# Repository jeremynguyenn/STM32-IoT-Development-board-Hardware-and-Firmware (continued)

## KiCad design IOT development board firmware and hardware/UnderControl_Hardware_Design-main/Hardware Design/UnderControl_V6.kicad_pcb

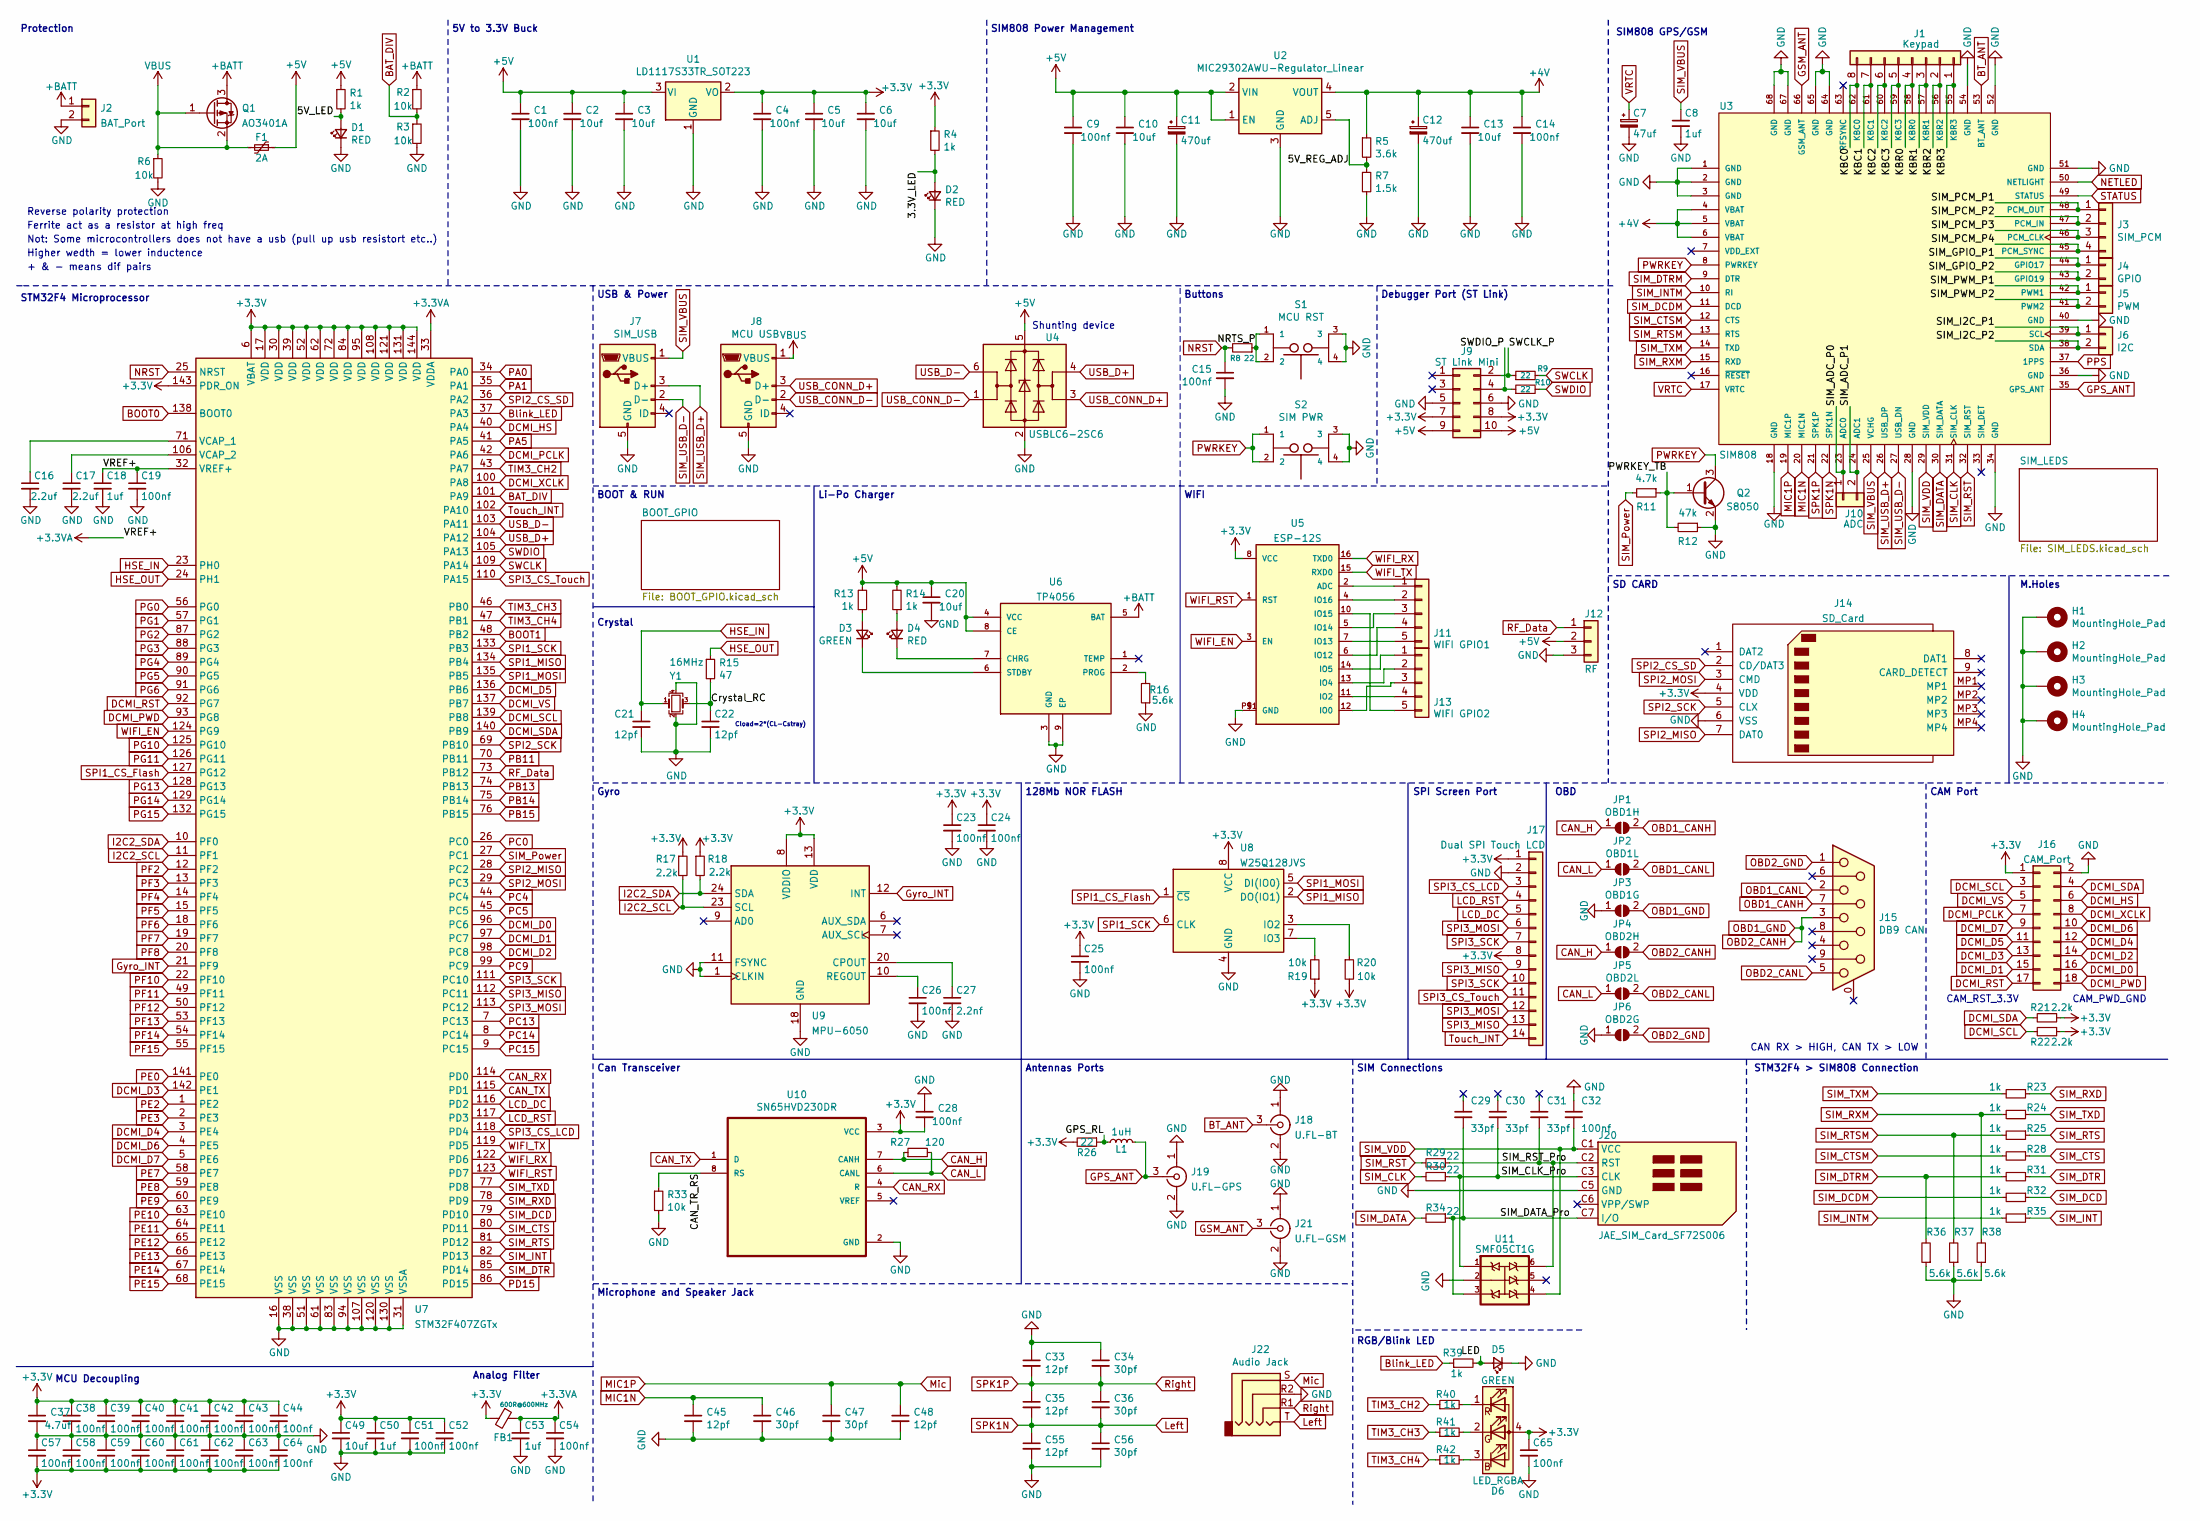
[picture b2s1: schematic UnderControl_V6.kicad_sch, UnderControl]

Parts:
C1, C4, C9, C14, C15, C19, C23, C24, C25, C26, C28, C32, C38, C39, C40, C41, C42, C43, C44, C51, C52, C54, C57, C58, C59, C60, C61, C62, C63, C64, C65: 100nf; C_0402_1005Metric; LCSC C1525
C2, C3, C5, C6, C10, C13, C20, C49: 10uf; C_0603_1608Metric; LCSC C19702
C7: 47uf; C_1206_3216Metric; LCSC C96123
C8, C18, C50, C53: 1uf; C_0402_1005Metric; LCSC C52923
C11, C12: 470uf; CP_Elec_6.3x7.7; LCSC C134738
C16, C17: 2.2uf; C_0402_1005Metric; LCSC C12530
C21, C22, C33, C35, C45, C48, C55: 12pf; C_0402_1005Metric; LCSC C1547
C27: 2.2nf; C_0402_1005Metric; LCSC C1531
C29, C30, C31: 33pf; C_0402_1005Metric; LCSC C1531
C34, C36, C46, C47, C56: 30pf; C_0402_1005Metric; LCSC C1570
C37: 4.7uf; C_0402_1005Metric; LCSC C23733
D1, D2, D4: RED; LED_0805_2012Metric; LCSC C84256
D3, D5: GREEN; LED_0603_1608Metric; LCSC C72043
D6: LED_RGBA; 19237R6GHBHCA012T; LCSC C60105
F1: 2A; Fuse_1206_3216Metric; LCSC C187595
FB1: 600R@600MHz; L_0805_2012Metric; LCSC C1017
H1, H2, H3, H4: MountingHole_Pad; MountingHole_2.5mm_Pad_Via
J1: Keypad; PinSocket_1x08_P2.54mm_Vertical
J2: BAT_Port; JST_B2B-XH-A(LF)(SN)
J3: SIM_PCM; PinHeader_1x04_P2.54mm_Vertical
J4: GPIO; PinHeader_1x02_P2.54mm_Vertical
J5: PWM; PinHeader_1x02_P2.54mm_Vertical
J6: I2C; PinHeader_1x02_P2.54mm_Vertical
J7: SIM_USB; AMPHENOL_10118194-0001LF; LCSC C132563
J8: MCU USB; AMPHENOL_10118194-0001LF; LCSC C132563
J9: ST Link Mini; PinSocket_2x05_P2.54mm_Horizontal
J10: ADC; PinHeader_1x02_P2.54mm_Vertical
J11: WIFI GPIO1; PinSocket_1x05_P2.54mm_Vertical
J12: RF; PinHeader_1x03_P2.54mm_Vertical
J13: WIFI GPIO2; PinSocket_1x05_P2.54mm_Vertical
J14: SD_Card; TF15X15; LCSC C111196
J15: DB9 CAN; DSUB-9_Female_Horizontal_P2.77x2.84mm_EdgePinOffset4.94mm_H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
J16: CAM_Port; PinSocket_2x09_P2.54mm_Vertical
J17: Dual SPI Touch LCD; PinSocket_1x14_P2.54mm_Vertical
J18: U.FL-BT; HRS_U.FL-R-SMT(01); LCSC C88374
J19: U.FL-GPS; HRS_U.FL-R-SMT(01); LCSC C88374
J20: JAE_SIM_Card_SF72S006; GCT_SIM8060-6-1-14-00-A; LCSC C410356
J21: U.FL-GSM; HRS_U.FL-R-SMT(01); LCSC C88374
J22: Audio Jack; Jack_3.5mm_PJ320D_Horizontal
JP1: OBD1H; SolderJumper-2_P1.3mm_Open_TrianglePad1.0x1.5mm
JP2: OBD1L; SolderJumper-2_P1.3mm_Open_TrianglePad1.0x1.5mm
JP3: OBD1G; SolderJumper-2_P1.3mm_Open_TrianglePad1.0x1.5mm
JP4: OBD2H; SolderJumper-2_P1.3mm_Open_TrianglePad1.0x1.5mm
JP5: OBD2L; SolderJumper-2_P1.3mm_Open_TrianglePad1.0x1.5mm
JP6: OBD2G; SolderJumper-2_P1.3mm_Open_TrianglePad1.0x1.5mm
L1: 1uH; L_0805_2012Metric; LCSC C1042
Q1: AO3401A; SOT-23; LCSC C15127
Q2: S8050; SOT-23; LCSC C2146
R1, R4, R13, R14, R23, R24, R25, R28, R31, R32, R35, R39, R40, R41, R42: 1k; R_0402_1005Metric; LCSC C11702
R2, R3, R6, R19, R20, R33: 10k; R_0402_1005Metric; LCSC C25744
R5: 3.6k; R_0603_1608Metric; LCSC C22980
R7: 1.5k; R_0603_1608Metric; LCSC C22843
R8, R9, R10, R26, R29, R30, R34: 22; R_0402_1005Metric; LCSC C25092
R11: 4.7k; R_0402_1005Metric; LCSC C25900
R12: 47k; R_0402_1005Metric; LCSC C25792
R15: 47; R_0402_1005Metric; LCSC C25118
R16, R36, R37, R38: 5.6k; R_0402_1005Metric; LCSC C25908
R17, R18, R21, R22: 2.2k; R_0402_1005Metric; LCSC C25879
R27: 120; R_0402_1005Metric; LCSC C25079
S1: MCU RST; SW_TL3342F160QG; LCSC C318884
S2: SIM PWR; SW_TL3342F160QG; LCSC C318884
U1: LD1117S33TR_SOT223; SOT-223-3_TabPin2; LCSC C86781
U2: MIC29302AWU-Regulator_Linear; TO-263-5_TabPin3; LCSC C411869
U3: SIM808; XCVR_SIM808; LCSC C126275
U4: USBLC6-2SC6; SOT-23-6; LCSC C2827654
U5: ESP-12S; LCSC C82898
U6: TP4056; SOIC127P600X175-9N; LCSC C16581
U7: STM32F407ZGTx; LQFP-144_20x20mm_P0.5mm; LCSC C19156
U8: W25Q128JVS; SOIC-8_5.23x5.23mm_P1.27mm; LCSC C97521
U9: MPU-6050; InvenSense_QFN-24_4x4mm_P0.5mm_NoMask; LCSC C24112
U10: SN65HVD230DR; SOIC127P599X175-8N; LCSC C12084
U11: SMF05CT1G; SOT65P210X110-6N; LCSC C15879
Y1: 16MHz; Crystal_SMD_3225-4Pin_3.2x2.5mm; LCSC C13738

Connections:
+3.3VA: C18.1, C19.1, C53.1, C54.1, FB1.1, U7.32 (VREF+), U7.33 (VDDA)
+3V3: C4.1, C5.1, C6.1, C23.1, C24.1, C25.1, C28.2, C37.1, C38.1, C39.1, C40.1, C41.1, C42.1, C43.1, C44.1, C49.1, C50.1, C51.1, C52.1, C57.2, C58.2, C59.2, C60.2, C61.2, C62.2, C63.2, C64.2, C65.1, D6.4 (A), FB1.2, J9.7, J9.8, J14.4 (VDD), J16.1, J17.1, J17.8, R4.1, R17.1, R18.1, R19.1, R20.2, R21.1, R22.1, R26.2, U1.2 (VO), U5.8 (VCC), U7.6 (VBAT), U7.17 (VDD), U7.30 (VDD), U7.39 (VDD), U7.52 (VDD), U7.62 (VDD), U7.72 (VDD), U7.84 (VDD), U7.95 (VDD), U7.108 (VDD), U7.121 (VDD), U7.131 (VDD), U7.143 (PDR_ON), U7.144 (VDD), U8.8 (VCC), U9.8 (VDDIO), U9.13 (VDD), U10.3 (VCC); also elsewhere on the board
+4V: C12.1, C13.1, C14.1, R5.1, U2.4 (VOUT), U3.4 (VBAT), U3.5 (VBAT), U3.6 (VBAT)
+5V: C1.1, C2.1, C3.1, C9.1, C10.1, C11.1, C20.1, F1.1, J9.9, J9.10, J12.2, R1.1, R13.2, R14.2, U1.3 (VI), U2.1 (EN), U2.2 (VIN), U4.5 (VBUS), U6.4 (VCC), U6.8 (CE); also elsewhere on the board
+BATT: J2.1, Q1.3 (D), R2.1, U6.5 (BAT)
/3.3V_LED: D2.2 (A), R4.2
/5V_LED: D1.2 (A), R1.2
/5V_REG_ADJ: R5.2, R7.1, U2.5 (ADJ)
/CAN_TR_RS: R33.1, U10.8 (RS)
/Crystal_RC: C22.1, R15.2, Y1.3
/GPS_RL: L1.1, R26.1
/KBC0: J1.8, U3.62 (KBC0)
/KBC1: J1.7, U3.61 (KBC1)
/KBC2: J1.6, U3.60 (KBC2)
/KBC3: J1.5, U3.59 (KBC3)
/KBR0: J1.4, U3.58 (KBR0)
/KBR1: J1.3, U3.57 (KBR1)
/KBR2: J1.2, U3.56 (KBR2)
/KBR3: J1.1, U3.55 (KBR3)
/LED: D5.2 (A), R39.2
/NRTS_P: R8.1, S1.1, S1.2
/PWRKEY_TB: Q2.1 (B), R11.1, R12.2
/SIM_ADC_P0: J10.1, U3.23 (ADC0)
/SIM_ADC_P1: J10.2, U3.24 (ADC1)
/SIM_CLK_Pro: C30.2, J20.C3 (CLK), R30.1, U11.1
/SIM_DATA_Pro: C29.2, J20.C7 (I/O), R34.1, U11.3
/SIM_GPIO_P1: J4.1, U3.44 (GPIO17)
/SIM_GPIO_P2: J4.2, U3.43 (GPIO19)
/SIM_I2C_P1: J6.1, U3.39 (SCL)
/SIM_I2C_P2: J6.2, U3.38 (SDA)
/SIM_PCM_P1: J3.1, U3.48 (PCM_OUT)
/SIM_PCM_P2: J3.2, U3.47 (PCM_IN)
/SIM_PCM_P3: J3.3, U3.46 (PCM_CLK)
/SIM_PCM_P4: J3.4, U3.45 (PCM_SYNC)
/SIM_PWM_P1: J5.1, U3.42 (PWM1)
/SIM_PWM_P2: J5.2, U3.41 (PWM2)
/SIM_RST_Pro: C31.2, J20.C2 (RST), R29.1, U11.6
/SWCLK_P: J9.2, R9.1
/SWDIO_P: J9.4, R10.1
BAT_DIV: R2.2, R3.1, U7.101 (PA9)
BOOT0: U7.138 (BOOT0); also elsewhere on the board
BOOT1: U7.48 (PB2); also elsewhere on the board
BT_ANT: J18.3 (GND), U3.53 (BT_ANT)
Blink_LED: R39.1, U7.37 (PA3)
CAN_H: JP1.1 (A), JP4.1 (A), R27.1, U10.7 (CANH)
CAN_L: JP2.1 (A), JP5.1 (A), R27.2, U10.6 (CANL)
CAN_RX: U7.114 (PD0), U10.4 (R)
CAN_TX: U7.115 (PD1), U10.1 (D)
DCMI_D0: J16.16, U7.96 (PC6)
DCMI_D1: J16.15, U7.97 (PC7)
DCMI_D2: J16.14, U7.98 (PC8)
DCMI_D3: J16.13, U7.142 (PE1)
DCMI_D4: J16.12, U7.3 (PE4)
DCMI_D5: J16.11, U7.136 (PB6)
DCMI_D6: J16.10, U7.4 (PE5)
DCMI_D7: J16.9, U7.5 (PE6)
DCMI_HS: J16.6, U7.40 (PA4)
DCMI_PCLK: J16.7, U7.42 (PA6)
DCMI_PWD: J16.18, U7.93 (PG8)
DCMI_RST: J16.17, U7.92 (PG7)
DCMI_SCL: J16.3, R22.2, U7.139 (PB8)
DCMI_SDA: J16.4, R21.2, U7.140 (PB9)
DCMI_VS: J16.5, U7.137 (PB7)
DCMI_XCLK: J16.8, U7.100 (PA8)
GND: C1.2, C2.2, C3.2, C4.2, C5.2, C6.2, C7.2, C8.2, C9.2, C10.2, C11.2, C12.2, C13.2, C14.2, C15.2, C16.2, C17.2, C18.2, C19.2, C20.2, C21.2, C22.2, C23.2, C24.2, C25.2, C26.2, C27.2, C28.1, C32.1, C33.1, C34.1, C37.2, C38.2, C39.2, C40.2, C41.2, C42.2, C43.2, C44.2, C45.2, C46.2, C47.2, C48.2, C49.2, C50.2, C51.2, C52.2, C53.2, C54.2, C55.2, C56.2, C57.1, C58.1, C59.1, C60.1, C61.1, C62.1, C63.1, C64.1, C65.2, D1.1 (K), D2.1 (K), D5.1 (K), H1.1, H2.1, H3.1, H4.1, J2.2, J7.5 (GND), J8.5 (GND), J9.5, J9.6, J12.3, J14.6 (VSS), J16.2, J17.2, J18.1 (In), J18.2 (GND), J19.1 (In), J19.2 (GND), J20.C5 (GND), J21.1 (In), J21.2 (GND), J22.R2, JP3.1 (A), JP6.1 (A), Q2.2 (E), R3.2, R6.2, R7.2, R12.1, R16.1, R33.2, R36.1, R37.1, R38.1, S1.3, S1.4, S2.3, S2.4, U1.1 (GND), U2.3 (GND), U3.1 (GND), U3.2 (GND), U3.3 (GND), U3.18 (GND), U3.28 (GND), U3.34 (GND), U3.36 (GND), U3.40 (GND), U3.51 (GND), U3.52 (GND), U3.54 (GND), U3.64 (GND), U3.65 (GND), U3.67 (GND), U3.68 (GND), U4.2 (GND), U5.9 (GND), U5.P$1 (GND), U6.3 (GND), U6.9 (EP), U7.16 (VSS), U7.31 (VSSA), U7.38 (VSS), U7.51 (VSS), U7.61 (VSS), U7.83 (VSS), U7.94 (VSS), U7.107 (VSS), U7.120 (VSS), U7.130 (VSS), U8.4 (GND), U9.1 (CLKIN), U9.11 (FSYNC), U9.18 (GND), U10.2 (GND), U11.2, Y1.2, Y1.4; also elsewhere on the board
GPS_ANT: J19.3 (GND), L1.2, U3.35 (GPS_ANT)
GSM_ANT: J21.3 (GND), U3.66 (GSM_ANT)
Gyro_INT: U7.21 (PF9), U9.12 (INT)
HSE_IN: C21.1, U7.23 (PH0), Y1.1
HSE_OUT: R15.1, U7.24 (PH1)
I2C2_SCL: R17.2, U7.11 (PF1), U9.23 (SCL)
I2C2_SDA: R18.2, U7.10 (PF0), U9.24 (SDA)
LCD_DC: J17.5, U7.116 (PD2)
LCD_RST: J17.4, U7.117 (PD3)
Left: C35.2, C36.2, C55.1, C56.1, J22.T, U3.22 (SPK1N)
MIC1N: C45.1, C46.1, U3.20 (MIC1N)
MIC1P: C47.1, C48.1, J22.S, U3.19 (MIC1P)
NETLED: U3.50 (NETLIGHT); also elsewhere on the board
NRST: C15.1, R8.2, U7.25 (NRST)
unnamed: C16.1, U7.71 (VCAP_1)
unnamed: C17.1, U7.106 (VCAP_2)
unnamed: C26.1, U9.10 (REGOUT)
unnamed: C27.1, U9.20 (CPOUT)
unnamed: D3.1 (K), U6.6 (STDBY)
unnamed: D3.2 (A), R13.1
unnamed: D4.1 (K), U6.7 (CHRG)
unnamed: D4.2 (A), R14.1
unnamed: D6.1 (RK), R40.2
unnamed: D6.2 (GK), R41.2
unnamed: D6.3 (BK), R42.2
unnamed: J11.1, U5.2 (ADC)
unnamed: J11.2, U5.4 (IO16)
unnamed: J11.3, U5.5 (IO14)
unnamed: J11.4, U5.6 (IO12)
unnamed: J11.5, U5.7 (IO13)
unnamed: J13.1, U5.14 (IO5)
unnamed: J13.2, U5.13 (IO4)
unnamed: J13.3, U5.12 (IO0)
unnamed: J13.4, U5.11 (IO2)
unnamed: J13.5, U5.10 (IO15)
unnamed: R16.2, U6.2 (PROG)
unnamed: R19.2, U8.7 (IO3)
unnamed: R20.1, U8.3 (IO2)
OBD1_CANH: J15.7, JP1.2 (B)
OBD1_CANL: J15.2, JP2.2 (B)
OBD1_GND: J15.3, JP3.2 (B), JP4.2 (B)
OBD2_CANL: J15.5, JP5.2 (B)
OBD2_GND: J15.1, JP6.2 (B)
PA0: U7.34 (PA0)
PA1: U7.35 (PA1)
PA5: U7.41 (PA5)
PB11: U7.70 (PB11)
PB13: U7.74 (PB13)
PB14: U7.75 (PB14)
PB15: U7.76 (PB15)
PC0: U7.26 (PC0)
PC4: U7.44 (PC4)
PC5: U7.45 (PC5)
PC9: U7.99 (PC9); also elsewhere on the board
PC13: U7.7 (PC13)
PC14: U7.8 (PC14)
PC15: U7.9 (PC15)
PD15: U7.86 (PD15)
PE0: U7.141 (PE0)
PE2: U7.1 (PE2)
PE3: U7.2 (PE3)
PE7: U7.58 (PE7); also elsewhere on the board
PE8: U7.59 (PE8); also elsewhere on the board
PE9: U7.60 (PE9)
PE10: U7.63 (PE10)
PE11: U7.64 (PE11); also elsewhere on the board
PE12: U7.65 (PE12)
PE13: U7.66 (PE13)
PE14: U7.67 (PE14)
PE15: U7.68 (PE15)
PF2: U7.12 (PF2); also elsewhere on the board
PF3: U7.13 (PF3); also elsewhere on the board
PF4: U7.14 (PF4); also elsewhere on the board
PF5: U7.15 (PF5)
PF6: U7.18 (PF6)
PF7: U7.19 (PF7); also elsewhere on the board
PF8: U7.20 (PF8); also elsewhere on the board
PF10: U7.22 (PF10)
PF11: U7.49 (PF11)
PF12: U7.50 (PF12)
PF13: U7.53 (PF13)
PF14: U7.54 (PF14)
PF15: U7.55 (PF15)
PG0: U7.56 (PG0); also elsewhere on the board
PG1: U7.57 (PG1); also elsewhere on the board
PG2: U7.87 (PG2); also elsewhere on the board
PG3: U7.88 (PG3); also elsewhere on the board
PG4: U7.89 (PG4); also elsewhere on the board
PG5: U7.90 (PG5); also elsewhere on the board
PG6: U7.91 (PG6)
PG10: U7.125 (PG10)
PG11: U7.126 (PG11)
PG13: U7.128 (PG13)
PG14: U7.129 (PG14)
PG15: U7.132 (PG15)
PPS: U3.37 (1PPS); also elsewhere on the board
PWRKEY: Q2.3 (C), S2.1, S2.2, U3.8 (PWRKEY)
RF_Data: J12.1, U7.73 (PB12)
Right: C33.2, C34.2, C35.1, C36.1, J22.R1, U3.21 (SPK1P)
SIM_CLK: R30.2, U3.31 (SIM_CLK)
SIM_CTS: R28.1, U7.80 (PD11)
SIM_CTSM: R28.2, U3.12 (CTS)
SIM_DATA: R34.2, U3.30 (SIM_DATA)
SIM_DCD: R32.1, U7.79 (PD10)
SIM_DCDM: R32.2, U3.11 (DCD)
SIM_DTR: R31.1, U7.85 (PD14)
SIM_DTRM: R31.2, R36.2, U3.9 (DTR)
SIM_INT: R35.1, U7.82 (PD13)
SIM_INTM: R35.2, U3.10 (RI)
SIM_Power: R11.2, U7.27 (PC1)
SIM_RST: R29.2, U3.32 (SIM_RST)
SIM_RTS: R25.1, U7.81 (PD12)
SIM_RTSM: R25.2, R37.2, U3.13 (RTS)
SIM_RXD: R23.1, U7.78 (PD9)
SIM_RXM: R24.2, R38.2, U3.15 (RXD)
SIM_TXD: R24.1, U7.77 (PD8)
SIM_TXM: R23.2, U3.14 (TXD)
SIM_USB_D+: J7.3 (D+), U3.26 (USB_DP)
SIM_USB_D-: J7.2 (D-), U3.27 (USB_DN)
SIM_VBUS: C8.1, J7.1 (VBUS), U3.25 (VCHG)
SIM_VDD: C32.2, J20.C1 (VCC), U3.29 (SIM_VDD), U11.4
SPI1_CS_Flash: U7.127 (PG12), U8.1 (~CS)
SPI1_MISO: U7.134 (PB4), U8.2 (DO(IO1))
SPI1_MOSI: U7.135 (PB5), U8.5 (DI(IO0))
SPI1_SCK: U7.133 (PB3), U8.6 (CLK)
SPI2_CS_SD: J14.2 (CD/DAT3), U7.36 (PA2)
SPI2_MISO: J14.7 (DAT0), U7.28 (PC2)
SPI2_MOSI: J14.3 (CMD), U7.29 (PC3)
SPI2_SCK: J14.5 (CLX), U7.69 (PB10)
SPI3_CS_LCD: J17.3, U7.118 (PD4)
SPI3_CS_Touch: J17.11, U7.110 (PA15)
SPI3_MISO: J17.9, J17.13, U7.112 (PC11)
SPI3_MOSI: J17.6, J17.12, U7.113 (PC12)
SPI3_SCK: J17.7, J17.10, U7.111 (PC10)
STATUS: U3.49 (STATUS); also elsewhere on the board
SWCLK: R9.2, U7.109 (PA14)
SWDIO: R10.2, U7.105 (PA13)
TIM3_CH2: R40.1, U7.43 (PA7)
TIM3_CH3: R41.1, U7.46 (PB0)
TIM3_CH4: R42.1, U7.47 (PB1)
Touch_INT: J17.14, U7.102 (PA10)
USB_CONN_D+: J8.3 (D+), U4.3 (I/O2)
USB_CONN_D-: J8.2 (D-), U4.1 (I/O1)
USB_D+: U4.4 (I/O2), U7.104 (PA12)
USB_D-: U4.6 (I/O1), U7.103 (PA11)
VBUS: F1.2, J8.1 (VBUS), Q1.1 (G), Q1.2 (S), R6.1
VRTC: C7.1, U3.17 (VRTC)
WIFI_EN: U5.3 (EN), U7.124 (PG9)
WIFI_RST: U5.1 (RST), U7.123 (PD7)
WIFI_RX: U5.16 (TXD0), U7.122 (PD6)
WIFI_TX: U5.15 (RXD0), U7.119 (PD5)

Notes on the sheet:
Shunting device
128Mb NOR FLASH
OBD
Antennas Ports
CAM_PWD_GND
CAM Port
Ferrite act as a resistor at high freq
Gyro
Crystal
SPI Screen Port
Buttons
CAN RX > HIGH, CAN TX > LOW
Not: Some microcontrollers does not have a usb (pull up usb resistort etc..)
BOOT & RUN
RGB/Blink LED
SD CARD
Protection
Higher wedth = lower inductence
WIFI
Microphone and Speaker Jack
M.Holes
CAM_RST_3.3V
Li-Po Charger
Reverse polarity protection
Can Transceiver
SIM808 Power Management
STM32F4 > SIM808 Connection
USB & Power
5V to 3.3V Buck
MCU Decoupling
STM32F4 Microprocessor
SIM808 GPS/GSM
Cload=2*(CL-Cstray)
Debugger Port (ST Link)
SIM Connections
Analog Filter
+ & - means dif pairs

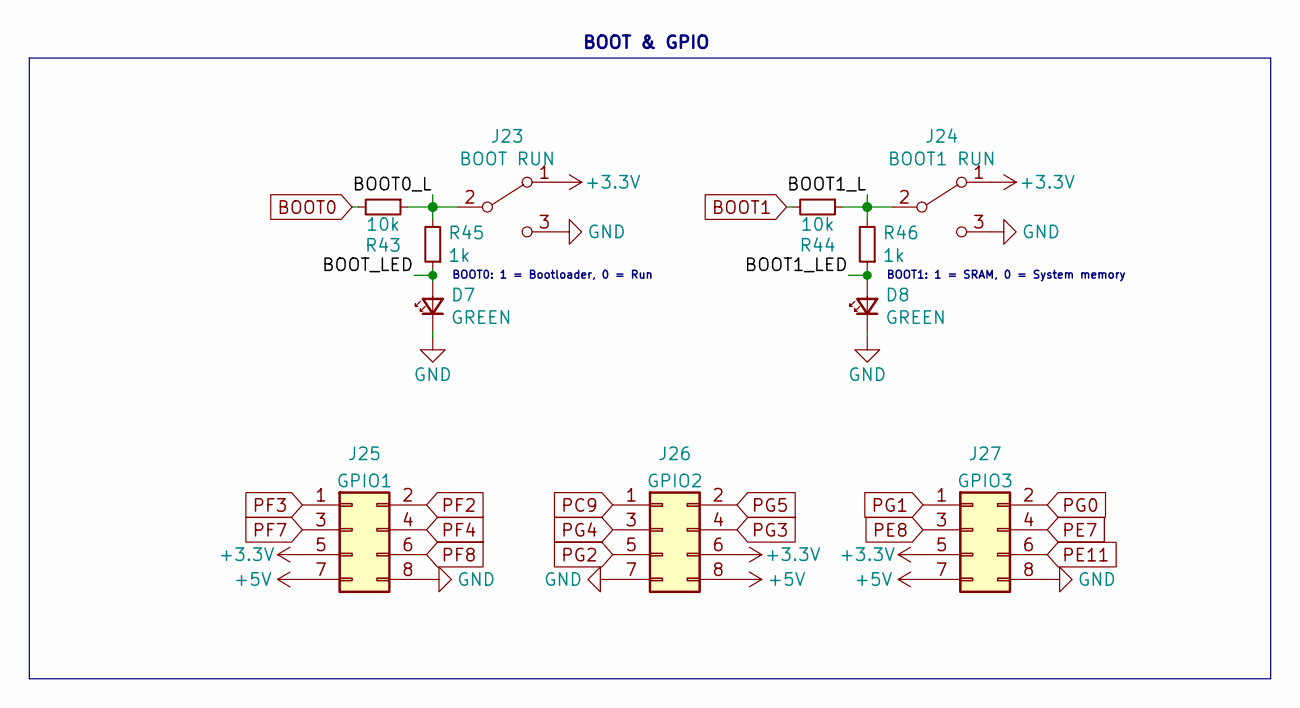
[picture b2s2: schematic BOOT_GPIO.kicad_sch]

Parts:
D7, D8: GREEN; LED_0603_1608Metric; LCSC C72043
J23: BOOT RUN; PinHeader_1x03_P2.54mm_Vertical
J24: BOOT1 RUN; PinHeader_1x03_P2.54mm_Vertical
J25: GPIO1; PinHeader_2x04_P2.54mm_Vertical
J26: GPIO2; PinHeader_2x04_P2.54mm_Vertical
J27: GPIO3; PinHeader_2x04_P2.54mm_Vertical
R43, R44: 10k; R_0402_1005Metric; LCSC C25744
R45, R46: 1k; R_0402_1005Metric; LCSC C11702

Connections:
+3V3: J23.1 (A), J24.1 (A), J25.5, J26.6, J27.5; also elsewhere on the board
+5V: J25.7, J26.8, J27.7; also elsewhere on the board
/BOOT_GPIO/BOOT0_L: J23.2 (B), R43.1, R45.2
/BOOT_GPIO/BOOT1_L: J24.2 (B), R44.1, R46.2
/BOOT_GPIO/BOOT1_LED: D8.2 (A), R46.1
/BOOT_GPIO/BOOT_LED: D7.2 (A), R45.1
BOOT0: R43.2; also elsewhere on the board
BOOT1: R44.2; also elsewhere on the board
GND: D7.1 (K), D8.1 (K), J23.3 (C), J24.3 (C), J25.8, J26.7, J27.8; also elsewhere on the board
PC9: J26.1; also elsewhere on the board
PE7: J27.4; also elsewhere on the board
PE8: J27.3; also elsewhere on the board
PE11: J27.6; also elsewhere on the board
PF2: J25.2; also elsewhere on the board
PF3: J25.1; also elsewhere on the board
PF4: J25.4; also elsewhere on the board
PF7: J25.3; also elsewhere on the board
PF8: J25.6; also elsewhere on the board
PG0: J27.2; also elsewhere on the board
PG1: J27.1; also elsewhere on the board
PG2: J26.5; also elsewhere on the board
PG3: J26.4; also elsewhere on the board
PG4: J26.3; also elsewhere on the board
PG5: J26.2; also elsewhere on the board

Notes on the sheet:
BOOT1: 1 = SRAM, 0 = System memory
BOOT & GPIO
BOOT0: 1 = Bootloader, 0 = Run

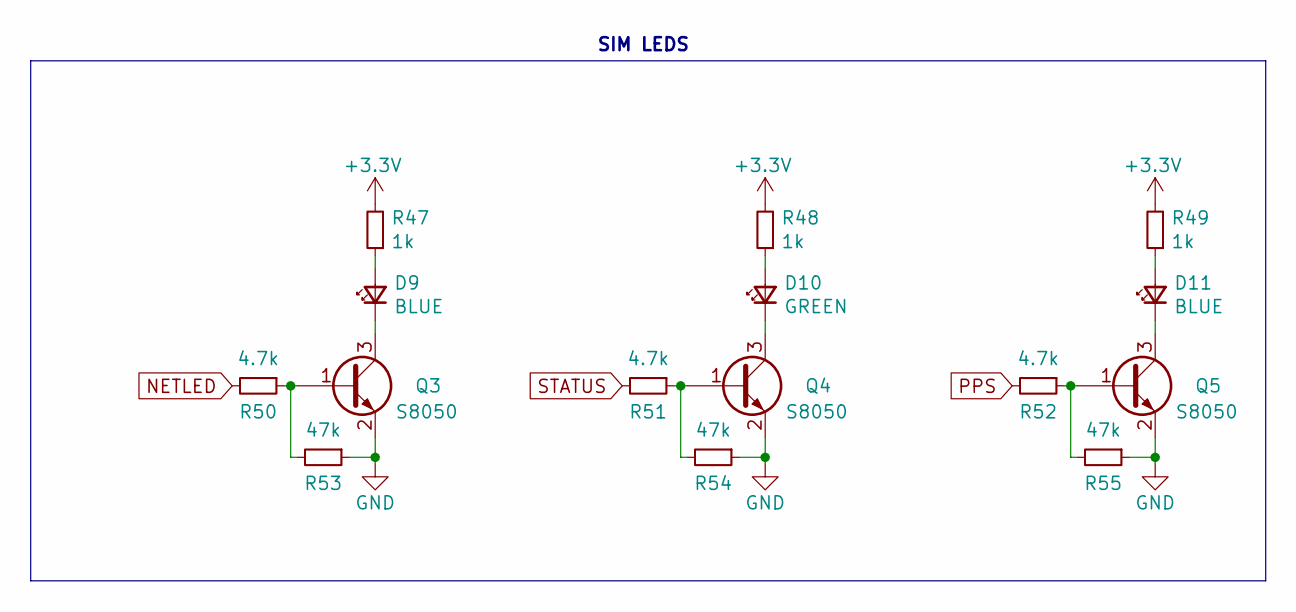
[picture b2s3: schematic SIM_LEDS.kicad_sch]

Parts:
D9, D11: BLUE; LED_0603_1608Metric; LCSC C72041
D10: GREEN; LED_0603_1608Metric; LCSC C72043
Q3, Q4, Q5: S8050; SOT-23; LCSC C2146
R47, R48, R49: 1k; R_0402_1005Metric; LCSC C11702
R50, R51, R52: 4.7k; R_0402_1005Metric; LCSC C25900
R53, R54, R55: 47k; R_0402_1005Metric; LCSC C25792

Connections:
+3V3: R47.2, R48.2, R49.2; also elsewhere on the board
GND: Q3.2 (E), Q4.2 (E), Q5.2 (E), R53.1, R54.1, R55.1; also elsewhere on the board
NETLED: R50.2; also elsewhere on the board
unnamed: D9.1 (K), Q3.3 (C)
unnamed: D9.2 (A), R47.1
unnamed: D10.1 (K), Q4.3 (C)
unnamed: D10.2 (A), R48.1
unnamed: D11.1 (K), Q5.3 (C)
unnamed: D11.2 (A), R49.1
unnamed: Q3.1 (B), R50.1, R53.2
unnamed: Q4.1 (B), R51.1, R54.2
unnamed: Q5.1 (B), R52.1, R55.2
PPS: R52.2; also elsewhere on the board
STATUS: R51.2; also elsewhere on the board

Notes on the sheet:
SIM LEDS

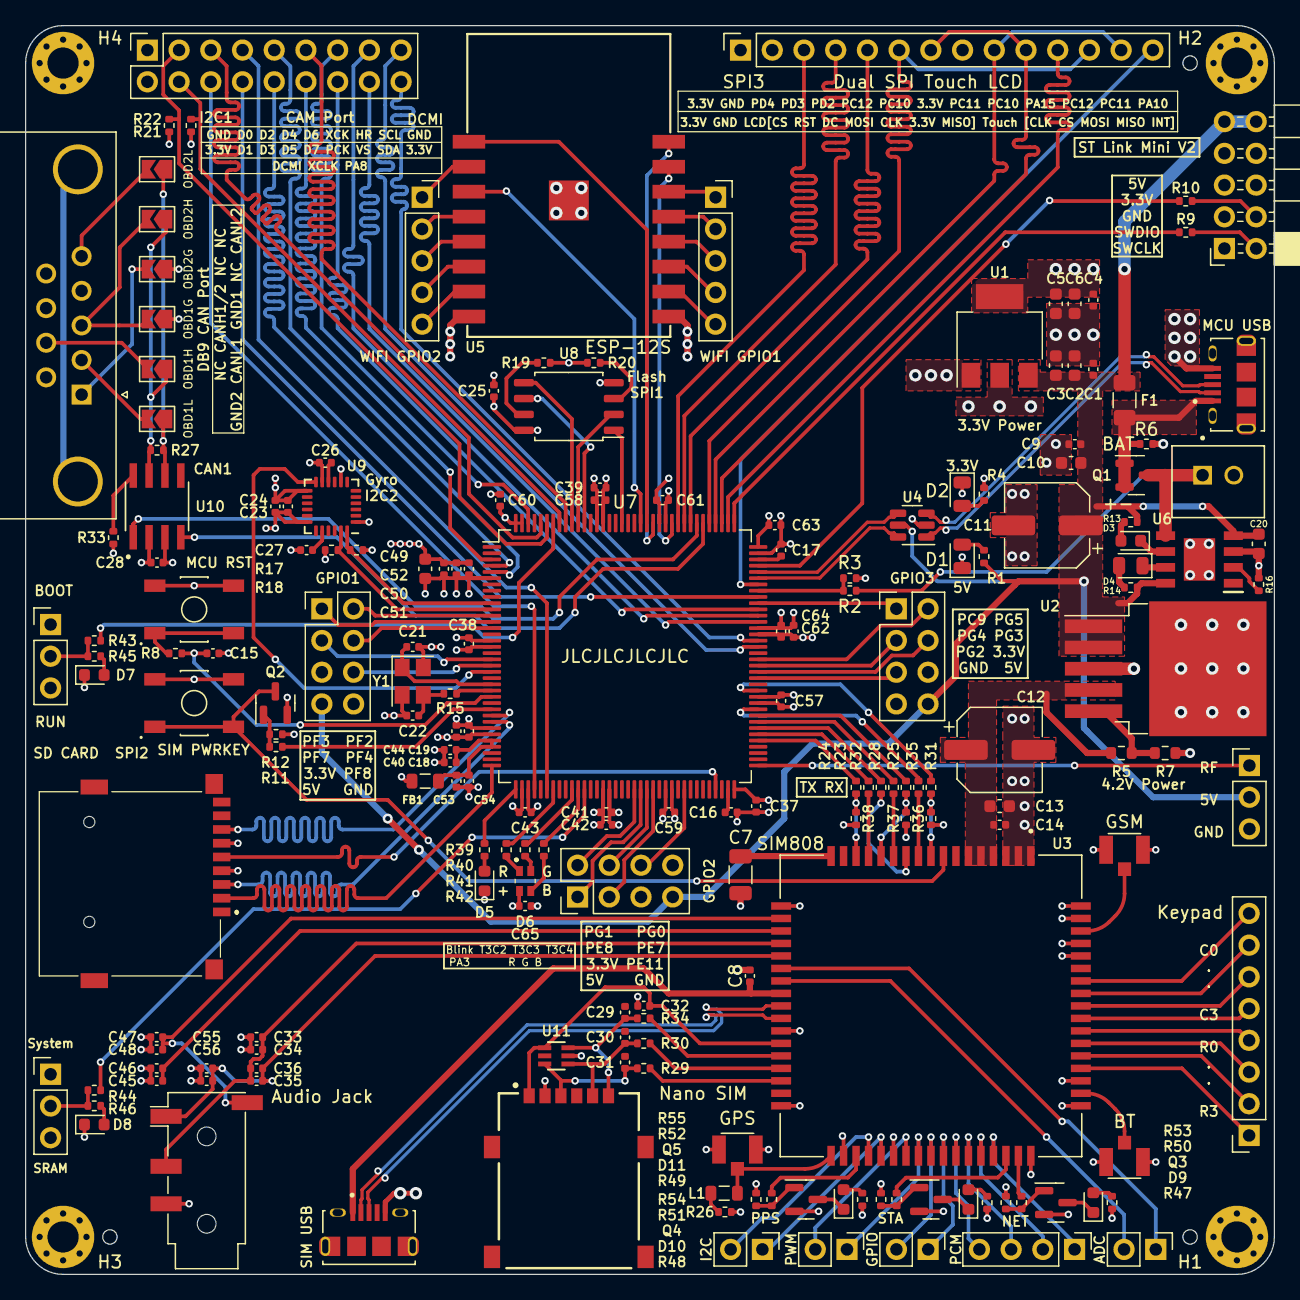
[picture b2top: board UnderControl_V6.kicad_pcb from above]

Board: 4 copper layers, 100.0 x 100.0 mm, 190 parts (0 on the bottom side), 192 nets.

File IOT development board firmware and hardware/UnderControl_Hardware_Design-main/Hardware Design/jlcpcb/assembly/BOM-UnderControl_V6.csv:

Comment,Designator,Footprint,LCSC
600R@600MHz,FB1,L_0805_2012Metric,C1017
1uH,L1,L_0805_2012Metric,C1042
SD_Card,J14,TF15X15,C111196
1k,"R1,R13,R14,R23,R24,R25,R28,R31,R32,R35,R39,R4,R40,R41,R42,R45,R46,R47,R48,R49",R_0402_1005Metric,C11702
SN65HVD230DR,U10,SOIC127P599X175-8N,C12084
2.2uf,"C16,C17",C_0402_1005Metric,C12530
SIM808,U3,XCVR_SIM808,C126275
SIM_USB,"J7,J8",AMPHENOL_10118194-0001LF,C132563
470uf,"C11,C12",CP_Elec_6.3x7.7,C134738
16MHz,Y1,Crystal_SMD_3225-4Pin_3.2x2.5mm,C13738
AO3401A,Q1,SOT-23,C15127
100nf,"C1,C14,C15,C19,C23,C24,C25,C26,C28,C32,C38,C39,C4,C40,C41,C42,C43,C44,C51,C52,C54,C57,C58,C59,C60,C61,C62,C63,C64,C65,C9",C_0402_1005Metric,C1525
2.2nf,"C27,C29,C30,C31",C_0402_1005Metric,C1531
12pf,"C21,C22,C33,C35,C45,C48,C55",C_0402_1005Metric,C1547
30pf,"C34,C36,C46,C47,C56",C_0402_1005Metric,C1570
SMF05CT1G,U11,SOT65P210X110-6N,C15879
TP4056,U6,SOIC127P600X175-9N,C16581
2A,F1,Fuse_1206_3216Metric,C187595
STM32F407ZGTx,U7,LQFP-144_20x20mm_P0.5mm,C19156
10uf,"C10,C13,C2,C20,C3,C49,C5,C6",C_0603_1608Metric,C19702
S8050,"Q2,Q3,Q4,Q5",SOT-23,C2146
1.5k,R7,R_0603_1608Metric,C22843
3.6k,R5,R_0603_1608Metric,C22980
4.7uf,C37,C_0402_1005Metric,C23733
MPU-6050,U9,InvenSense_QFN-24_4x4mm_P0.5mm_NoMask,C24112
120,R27,R_0402_1005Metric,C25079
22,"R10,R26,R29,R30,R34,R8,R9",R_0402_1005Metric,C25092
47,R15,R_0402_1005Metric,C25118
10k,"R19,R2,R20,R3,R33,R43,R44,R6",R_0402_1005Metric,C25744
47k,"R12,R53,R54,R55",R_0402_1005Metric,C25792
2.2k,"R17,R18,R21,R22",R_0402_1005Metric,C25879
4.7k,"R11,R50,R51,R52",R_0402_1005Metric,C25900
5.6k,"R16,R36,R37,R38",R_0402_1005Metric,C25908
USBLC6-2SC6,U4,SOT-23-6,C2827654
MCU RST,"S1,S2",SW_TL3342F160QG,C318884
JAE_SIM_Card_SF72S006,J20,GCT_SIM8060-6-1-14-00-A,C410356
MIC29302AWU-Regulator_Linear,U2,TO-263-5_TabPin3,C411869
1uf,"C18,C50,C53,C8",C_0402_1005Metric,C52923
LED_RGBA,D6,19237R6GHBHCA012T,C60105
BLUE,"D11,D9",LED_0603_1608Metric,C72041
GREEN,"D10,D3,D5,D7,D8",LED_0603_1608Metric,C72043
ESP-12S,U5,ESP-12S,C82898
RED,"D1,D2,D4",LED_0805_2012Metric,C84256
LD1117S33TR_SOT223,U1,SOT-223-3_TabPin2,C86781
U.FL-BT,"J18,J19,J21",HRS_U.FL-R-SMT(01),C88374
47uf,C7,C_1206_3216Metric,C96123
W25Q128JVS,U8,SOIC-8_5.23x5.23mm_P1.27mm,C97521
WIFI GPIO2,J13,PinSocket_1x05_P2.54mm_Vertical,
OBD2L,JP5,SolderJumper-2_P1.3mm_Open_TrianglePad1.0x1.5mm,
SIM_PCM,J3,PinHeader_1x04_P2.54mm_Vertical,
DB9 CAN,J15,DSUB-9_Female_Horizontal_P2.77x2.84mm_EdgePinOffset4.94mm_Housed_MountingHolesOffset7.48mm,
Keypad,J1,PinSocket_1x08_P2.54mm_Vertical,
GPIO3,J27,PinHeader_2x04_P2.54mm_Vertical,
CAM_Port,J16,PinSocket_2x09_P2.54mm_Vertical,
GPIO,J4,PinHeader_1x02_P2.54mm_Vertical,
Dual SPI Touch LCD,J17,PinSocket_1x14_P2.54mm_Vertical,
BOOT1 RUN,J24,PinHeader_1x03_P2.54mm_Vertical,
PWM,J5,PinHeader_1x02_P2.54mm_Vertical,
RF,J12,PinHeader_1x03_P2.54mm_Vertical,
ADC,J10,PinHeader_1x02_P2.54mm_Vertical,
OBD1G,JP3,SolderJumper-2_P1.3mm_Open_TrianglePad1.0x1.5mm,
ST Link Mini,J9,PinSocket_2x05_P2.54mm_Horizontal,
MountingHole_Pad,H1,MountingHole_2.5mm_Pad_Via,
OBD2G,JP6,SolderJumper-2_P1.3mm_Open_TrianglePad1.0x1.5mm,
OBD2H,JP4,SolderJumper-2_P1.3mm_Open_TrianglePad1.0x1.5mm,
I2C,J6,PinHeader_1x02_P2.54mm_Vertical,
MountingHole_Pad,H3,MountingHole_2.5mm_Pad_Via,
MountingHole_Pad,H4,MountingHole_2.5mm_Pad_Via,
WIFI GPIO1,J11,PinSocket_1x05_P2.54mm_Vertical,
OBD1H,JP1,SolderJumper-2_P1.3mm_Open_TrianglePad1.0x1.5mm,
BAT_Port,J2,JST_B2B-XH-A(LF)(SN),
MountingHole_Pad,H2,MountingHole_2.5mm_Pad_Via,
Audio Jack,J22,Jack_3.5mm_PJ320D_Horizontal,
OBD1L,JP2,SolderJumper-2_P1.3mm_Open_TrianglePad1.0x1.5mm,
BOOT RUN,J23,PinHeader_1x03_P2.54mm_Vertical,
GPIO2,J26,PinHeader_2x04_P2.54mm_Vertical,
GPIO1,J25,PinHeader_2x04_P2.54mm_Vertical,

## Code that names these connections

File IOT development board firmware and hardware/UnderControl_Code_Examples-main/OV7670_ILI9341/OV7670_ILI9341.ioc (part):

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Mcu.Name=STM32F407Z(E-G)Tx
Mcu.Package=LQFP144
Mcu.UserName=STM32F407ZGTx
PA10.GPIOParameters=GPIO_Label
PA10.GPIO_Label=TOUCH_IRQ
PA10.Signal=GPIO_Input
PA11.Mode=Device_Only
PA11.Signal=USB_OTG_FS_DM
PA12.Mode=Device_Only
PA12.Signal=USB_OTG_FS_DP
PA13.Mode=Serial_Wire
PA13.Signal=SYS_JTMS-SWDIO
PA14.Mode=Serial_Wire
PA14.Signal=SYS_JTCK-SWCLK
PA15.GPIOParameters=GPIO_Label
PA15.GPIO_Label=TOUCH_CS
PA15.Signal=GPIO_Output
PA2.GPIOParameters=PinState,GPIO_Label
PA2.GPIO_Label=SD_CS
PA2.PinState=GPIO_PIN_SET
PA2.Signal=GPIO_Output
PA3.GPIOParameters=PinState,GPIO_Label,GPIO_ModeDefaultOutputPP
PA3.GPIO_Label=USER_LED
PA3.GPIO_ModeDefaultOutputPP=GPIO_MODE_OUTPUT_OD
PA3.PinState=GPIO_PIN_SET
PA3.Signal=GPIO_Output
PA4.GPIOParameters=GPIO_Speed,GPIO_PuPd
PA4.GPIO_PuPd=GPIO_PULLDOWN
PA4.GPIO_Speed=GPIO_SPEED_FREQ_VERY_HIGH
PA4.Mode=Slave_8_bits_External_Synchro
PA4.Signal=DCMI_HSYNC
PA6.GPIOParameters=GPIO_Speed,GPIO_PuPd
PA6.GPIO_PuPd=GPIO_PULLDOWN
PA6.GPIO_Speed=GPIO_SPEED_FREQ_VERY_HIGH
PA6.Mode=Slave_8_bits_External_Synchro
PA6.Signal=DCMI_PIXCLK
PA8.GPIOParameters=GPIO_Speed
PA8.GPIO_Speed=GPIO_SPEED_FREQ_VERY_HIGH
PA8.Mode=Clock-out-1
PA8.Signal=RCC_MCO_1
PB10.GPIOParameters=GPIO_PuPd,GPIO_Label
PB10.GPIO_Label=SD_SCK
PB10.GPIO_PuPd=GPIO_PULLDOWN
PB10.Mode=Full_Duplex_Master
PB10.Signal=SPI2_SCK
PB6.GPIOParameters=GPIO_Speed,GPIO_PuPd
PB6.GPIO_PuPd=GPIO_PULLDOWN
PB6.GPIO_Speed=GPIO_SPEED_FREQ_VERY_HIGH
PB6.Mode=Slave_8_bits_External_Synchro
PB6.Signal=DCMI_D5
PB7.GPIOParameters=GPIO_Speed,GPIO_PuPd
PB7.GPIO_PuPd=GPIO_PULLDOWN
PB7.GPIO_Speed=GPIO_SPEED_FREQ_VERY_HIGH
PB7.Mode=Slave_8_bits_External_Synchro
PB7.Signal=DCMI_VSYNC
PB8.GPIOParameters=GPIO_Pu
PB8.GPIO_Pu=GPIO_PULLUP
PB8.Mode=I2C
PB8.Signal=I2C1_SCL
PB9.GPIOParameters=GPIO_Pu
PB9.GPIO_Pu=GPIO_PULLUP
PB9.Mode=I2C
PB9.Signal=I2C1_SDA
PC10.GPIOParameters=GPIO_Label
PC10.GPIO_Label=LCD_SCK
PC10.Mode=Full_Duplex_Master
PC10.Signal=SPI3_SCK
PC11.GPIOParameters=GPIO_Label
PC11.GPIO_Label=LCD_MISO
PC11.Mode=Full_Duplex_Master
PC11.Signal=SPI3_MISO
PC12.GPIOParameters=GPIO_Label
PC12.GPIO_Label=LCD_MOSI
PC12.Mode=Full_Duplex_Master
PC12.Signal=SPI3_MOSI
PC2.GPIOParameters=GPIO_Speed,GPIO_PuPd,GPIO_Label
PC2.GPIO_Label=SD_MISO
PC2.GPIO_PuPd=GPIO_PULLUP
PC2.GPIO_Speed=GPIO_SPEED_FREQ_VERY_HIGH
PC2.Mode=Full_Duplex_Master
PC2.Signal=SPI2_MISO
PC3.GPIOParameters=GPIO_Speed,GPIO_PuPd,GPIO_Label
PC3.GPIO_Label=SD_MOSI
PC3.GPIO_PuPd=GPIO_PULLUP
PC3.GPIO_Speed=GPIO_SPEED_FREQ_VERY_HIGH
PC3.Mode=Full_Duplex_Master
PC3.Signal=SPI2_MOSI
PC6.GPIOParameters=GPIO_Speed,GPIO_PuPd
PC6.GPIO_PuPd=GPIO_PULLDOWN
PC6.GPIO_Speed=GPIO_SPEED_FREQ_VERY_HIGH
PC6.Mode=Slave_8_bits_External_Synchro
PC6.Signal=DCMI_D0
PC7.GPIOParameters=GPIO_Speed,GPIO_PuPd
PC7.GPIO_PuPd=GPIO_PULLDOWN
PC7.GPIO_Speed=GPIO_SPEED_FREQ_VERY_HIGH
PC7.Mode=Slave_8_bits_External_Synchro
PC7.Signal=DCMI_D1
PC8.GPIOParameters=GPIO_Speed,GPIO_PuPd
PC8.GPIO_PuPd=GPIO_PULLDOWN
PC8.GPIO_Speed=GPIO_SPEED_FREQ_VERY_HIGH
PC8.Mode=Slave_8_bits_External_Synchro
PC8.Signal=DCMI_D2
PD2.GPIOParameters=GPIO_Speed,PinState,GPIO_Label
PD2.GPIO_Label=LCD_DC
PD2.GPIO_Speed=GPIO_SPEED_FREQ_VERY_HIGH
PD2.PinState=GPIO_PIN_SET
PD2.Signal=GPIO_Output
PD3.GPIOParameters=GPIO_Speed,PinState,GPIO_Label
PD3.GPIO_Label=LCD_RST
PD3.GPIO_Speed=GPIO_SPEED_FREQ_VERY_HIGH
PD3.PinState=GPIO_PIN_SET
PD3.Signal=GPIO_Output
PD4.GPIOParameters=GPIO_Speed,PinState,GPIO_Label
PD4.GPIO_Label=LCD_CS
PD4.GPIO_Speed=GPIO_SPEED_FREQ_VERY_HIGH
PD4.PinState=GPIO_PIN_SET
PD4.Signal=GPIO_Output
PE1.GPIOParameters=GPIO_Speed,GPIO_PuPd
PE1.GPIO_PuPd=GPIO_PULLDOWN
PE1.GPIO_Speed=GPIO_SPEED_FREQ_VERY_HIGH
PE1.Mode=Slave_8_bits_External_Synchro
PE1.Signal=DCMI_D3
PE4.GPIOParameters=GPIO_Speed,GPIO_PuPd
PE4.GPIO_PuPd=GPIO_PULLDOWN
PE4.GPIO_Speed=GPIO_SPEED_FREQ_VERY_HIGH
PE4.Mode=Slave_8_bits_External_Synchro
PE4.Signal=DCMI_D4
PE5.GPIOParameters=GPIO_Speed,GPIO_PuPd
PE5.GPIO_PuPd=GPIO_PULLDOWN
PE5.GPIO_Speed=GPIO_SPEED_FREQ_VERY_HIGH
PE5.Mode=Slave_8_bits_External_Synchro
PE5.Signal=DCMI_D6
PE6.GPIOParameters=GPIO_Speed,GPIO_PuPd
PE6.GPIO_PuPd=GPIO_PULLDOWN
PE6.GPIO_Speed=GPIO_SPEED_FREQ_VERY_HIGH
PE6.Mode=Slave_8_bits_External_Synchro
PE6.Signal=DCMI_D7
PE7.GPIOParameters=GPIO_PuPd,GPIO_Label
PE7.GPIO_Label=BTN_ROT
PE7.GPIO_PuPd=GPIO_PULLUP
PE7.Signal=GPIO_Input
PF7.GPIOParameters=GPIO_PuPd,GPIO_Label
PF7.GPIO_Label=BTN_CAP
PF7.GPIO_PuPd=GPIO_PULLUP
PF7.Signal=GPIO_Input
PF8.GPIOParameters=GPIO_PuPd,GPIO_Label
PF8.GPIO_Label=BTN_MODE
PF8.GPIO_PuPd=GPIO_PULLUP
PF8.Signal=GPIO_Input
PG0.GPIOParameters=GPIO_Label
PG0.GPIO_Label=ROT_A
PG0.Signal=GPIO_Input
PG1.GPIOParameters=GPIO_Label
PG1.GPIO_Label=ROT_B
PG1.Signal=GPIO_Input
PG7.GPIOParameters=GPIO_PuPd,GPIO_Label
PG7.GPIO_Label=CAMERA_RESET
PG7.GPIO_PuPd=GPIO_PULLUP
PG7.Signal=GPIO_Output
PG8.GPIOParameters=GPIO_PuPd,GPIO_Label
PG8.GPIO_Label=CAMERA_PWD
PG8.GPIO_PuPd=GPIO_PULLDOWN
PG8.Signal=GPIO_Output
PH0-OSC_IN.Mode=HSE-External-Oscillator
PH0-OSC_IN.Signal=RCC_OSC_IN
PH1-OSC_OUT.Mode=HSE-External-Oscillator
PH1-OSC_OUT.Signal=RCC_OSC_OUT
RCC.HSE_VALUE=16000000
RCC.SYSCLKFreq_VALUE=168000000
RCC.SYSCLKSource=RCC_SYSCLKSOURCE_PLLCLK
board=custom

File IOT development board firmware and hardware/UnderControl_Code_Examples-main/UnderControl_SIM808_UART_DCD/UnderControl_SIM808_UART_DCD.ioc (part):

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Mcu.Name=STM32F407Z(E-G)Tx
Mcu.Package=LQFP144
Mcu.UserName=STM32F407ZGTx
PA11.Mode=Device_Only
PA11.Signal=USB_OTG_FS_DM
PA12.Mode=Device_Only
PA12.Signal=USB_OTG_FS_DP
PA13.Mode=Serial_Wire
PA13.Signal=SYS_JTMS-SWDIO
PA14.Mode=Serial_Wire
PA14.Signal=SYS_JTCK-SWCLK
PA3.GPIOParameters=GPIO_Label
PA3.GPIO_Label=LED
PA3.Signal=GPIO_Output
PD8.Mode=Asynchronous
PD8.Signal=USART3_TX
PD9.Mode=Asynchronous
PD9.Signal=USART3_RX
PH0-OSC_IN.Mode=HSE-External-Oscillator
PH0-OSC_IN.Signal=RCC_OSC_IN
PH1-OSC_OUT.Mode=HSE-External-Oscillator
PH1-OSC_OUT.Signal=RCC_OSC_OUT
RCC.HSE_VALUE=16000000
RCC.SYSCLKFreq_VALUE=168000000
RCC.SYSCLKSource=RCC_SYSCLKSOURCE_PLLCLK
board=custom

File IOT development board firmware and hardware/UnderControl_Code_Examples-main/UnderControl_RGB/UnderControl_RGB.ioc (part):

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Mcu.Name=STM32F407Z(E-G)Tx
Mcu.Package=LQFP144
Mcu.UserName=STM32F407ZGTx
PA13.Mode=Serial_Wire
PA13.Signal=SYS_JTMS-SWDIO
PA14.Mode=Serial_Wire
PA14.Signal=SYS_JTCK-SWCLK
PA7.GPIOParameters=GPIO_Label
PA7.GPIO_Label=LED1
PA7.Signal=GPIO_Output
PB0.GPIOParameters=GPIO_Label
PB0.GPIO_Label=LED2
PB0.Signal=GPIO_Output
PB1.GPIOParameters=GPIO_Label
PB1.GPIO_Label=LED3
PB1.Signal=GPIO_Output
PH0-OSC_IN.Mode=HSE-External-Oscillator
PH0-OSC_IN.Signal=RCC_OSC_IN
PH1-OSC_OUT.Mode=HSE-External-Oscillator
PH1-OSC_OUT.Signal=RCC_OSC_OUT
RCC.HSE_VALUE=16000000
RCC.SYSCLKFreq_VALUE=168000000
RCC.SYSCLKSource=RCC_SYSCLKSOURCE_PLLCLK
board=custom

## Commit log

2025-09-02 finaldev
2025-09-02 Create LICENSE
